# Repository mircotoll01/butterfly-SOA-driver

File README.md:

# Overview
This is an experimental slave module used to drive a optical devices with a butterfly package and integrated TEC. The driver can be operated from the header connector on the side.
The board was initially thought as a Laser Diode driver encased in butterfly packages, which usually integrate both the LD and a Peltier cell.
Since there is no standard pinouts in butterfly-type packages, this board routes all its power outputs and inputs to a row of headers, and all butterfly pins are routed to open headers as well, so that it is possible to route different parts of the board to different butterfly pins, whose position is numbered and indicated on silkscreen. 

# Pinout

|PIN|USAGE|INFO|
|-|-|-|
|1|3V3|Logic power supply, mandatory for the DAC that sets the optical device voltage|
|2|SCL|I2C clock pin for the DAC|
|3|SDA|I2C data pin for the DAC|
|4|$\overline{LDAC}$|Enable DAC register write mode|
|5|$RDY/\overline{BSY}$|This pin gives information on the DAC status|
|6|GND||
|7|TEC_EN|Enabling input for TEC|
|8|LD_MOD|LT3743's PWM input, when this signal is set to low all switching is disabled. Pull high if you don't plan to use it|
|9|CTRL_SEL|LT3743's switch for output voltage selection. The board has a double output capacitor topology that can be used to switch between two voltages. Useful if there is the need to keep an LD under the lasing threshold and periodically switch to a higher voltage.|
|10|ILD_MON|optical device current monitor|
|11|LD_EN|LT3743's enable pin|
|12|UNDRTMP_ALM|Sets if the temperature gets lower than a certain setpoint|
|13|OVRTMP_ALM|Sets if the temperature gets higher than a certain setpoint|
|14|ITEC_MON|TEC current monitor|

# Usage

The board was tested with a Basys3 as a master module and the firmware is available in this repository. If a basys3 is used to operate this driver connect its output pins in the following way (declared in the bays3's constraint file):

JA1     &rarr; OVRTMP_ALM  \
JA2     &rarr; UNDRTMP_ALM \
JA3     &rarr; LD_EN \
JA4     &rarr; CTRL_SEL \
JA5     &rarr; GND \
JA6     &rarr; 3V3 \
JA8     &rarr; TEC_EN \
JA9     &rarr; SDA \
JA10    &rarr; SCL \
JB1     &rarr; $\overline{LDAC}$  
\
To control the board with the Basys3 simply connect these pins and connect the board to the computer via USB. The given firmware will provide a rudimental serial interface that will control the state of the driver.
A simple python script can do the trick. the following one will work on linux:

```
import serial

ser = serial.Serial('/dev/ttyUSB1', baudrate=9600, bytesize=serial.EIGHTBITS, parity=serial.PARITY_NONE, stopbits=serial.STOPBITS_TWO,timeout=10)

while True:
    packet = bytearray(input("Waiting for a command: ").encode("ascii") + b'\n')

    ser.write(packet)

    for i in packet:
        print(ser.read())
    
```

#### Update
Now this repo provides a python script that gives a console to the user to send commands and see current parameters. The requirements for the python script are the following: 

- curses
- threading
- pyserial
- time
- re

### Command list

|COMMAND|INFO|
|-|-|
|OFF|Pulls LD_EN to low, disables all switching functions. Any other command will set LD_EN back to high|
|CCC|Activates the part of the circuit that supplies costant current to the optical component|
|TEC|Activates the Thermo-Electric Controller|
|PWM|Sets PWM mode with a certain duty cycle, set CTLL voltage first to operate the optical device in this mode|
|SET|Sets the selected register of the DAC to a set value|
|DBL|Sets double output voltage mode, the low and high thresholds have to be set first|

The SET command will accept the following attributes:

|ATTRIBUTE|INFO|
|-|-|
|CTLL| Modifies the lower voltage threshold CTRL_L. Note: this pin is internally clamped to 1.5V by the LT3743|
|CTLH| Modifies the higher voltage threshold CTRL_H. Note: this pin is internally clamped to 1.5V by the LT3743|
|TSET| Sets the voltage setpoint for the TEC's PID controller|
|MAXV| Sets the TEC's maximum operating voltage|

### Syntax
<table>
    <tr>
        <th>BASE COMMAND</th>
        <th>FIRST ATTRIBUTE</th>
        <th>SECOND ATTRIBUTE</th>
    </tr>
    <tr>
        <td>OFF</td>
        <td>None</td>
        <td>None</td>
    </tr>
    <tr>
        <td>CCC</td>
        <td>ON/OFF</td>
        <td>None</td>
    </tr>
    <tr>
        <td>TEC</td>
        <td>ON/OFF</td>
        <td>None</td>
    </tr>
    <tr>
        <td rowspan="4">SET</td>
        <td>CTLL</td>
        <td rowspan="2">Integer from 0 to 1500, which corresponds to a voltage output from the DAC that goes from 0 to 1.5V. This voltage sets the inductor current which charges its corresponding output capacitor.
        </td>
    </tr>
    <tr>
        <td>CTLH</td>
        <td></td>
    </tr>
    <tr>
        <td>TSET</td>
        <td>Integer from 0 to 1500, which corresponds to a voltage output from the DAC that goes from 0 to 1.5V.</td>
    </tr>
    <tr>
        <td>MAXV</td>
        <td>Integer from 0 to 5000. The program scales it down to reach a voltage output from the DAC that goes from 0 to 1.250V. 
        Since TEC voltage is set to 4*MAXV the range 0-5V range can be achieved.</td>
    </tr>
    <tr>
        <td>PWM</td>
        <td>Integer encoded in three ciphers from 000 to 100</td>
        <td>None</td>
    </tr>
    <tr>
        <td>DBL</td>
        <td>Integer encoded in three ciphers from 000 to 100</td>
        <td>None</td>
    </tr>
</table>

#### Update Note
The commands are not case sensitive anymore

### Examples

Turn on a SOA or an LD:

```
CCC ON
PWM 100
```

Enable PWM modulation

```
CCC ON
PWM XXX
```

Enable double threshold modulation

```
CCC ON
DBL XXX
```

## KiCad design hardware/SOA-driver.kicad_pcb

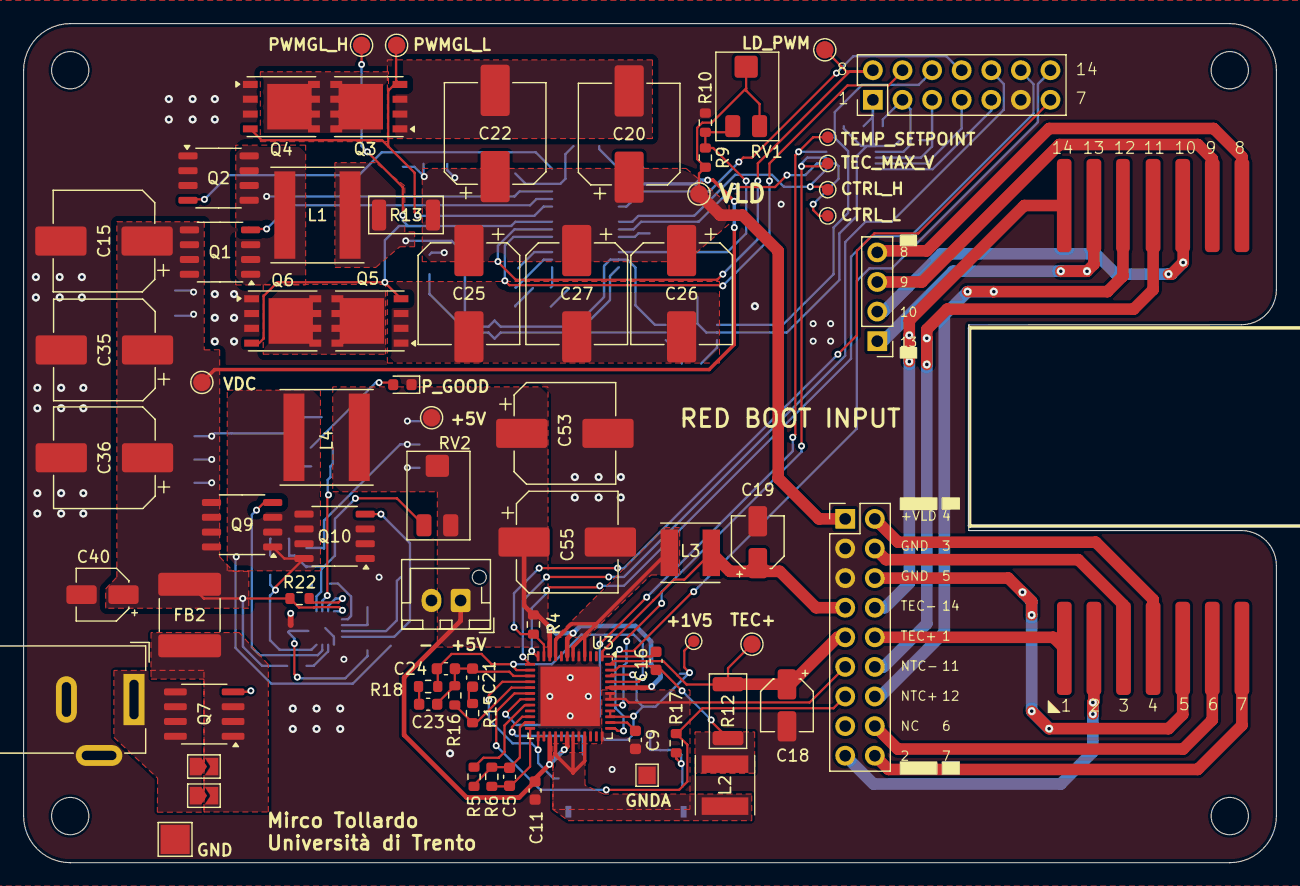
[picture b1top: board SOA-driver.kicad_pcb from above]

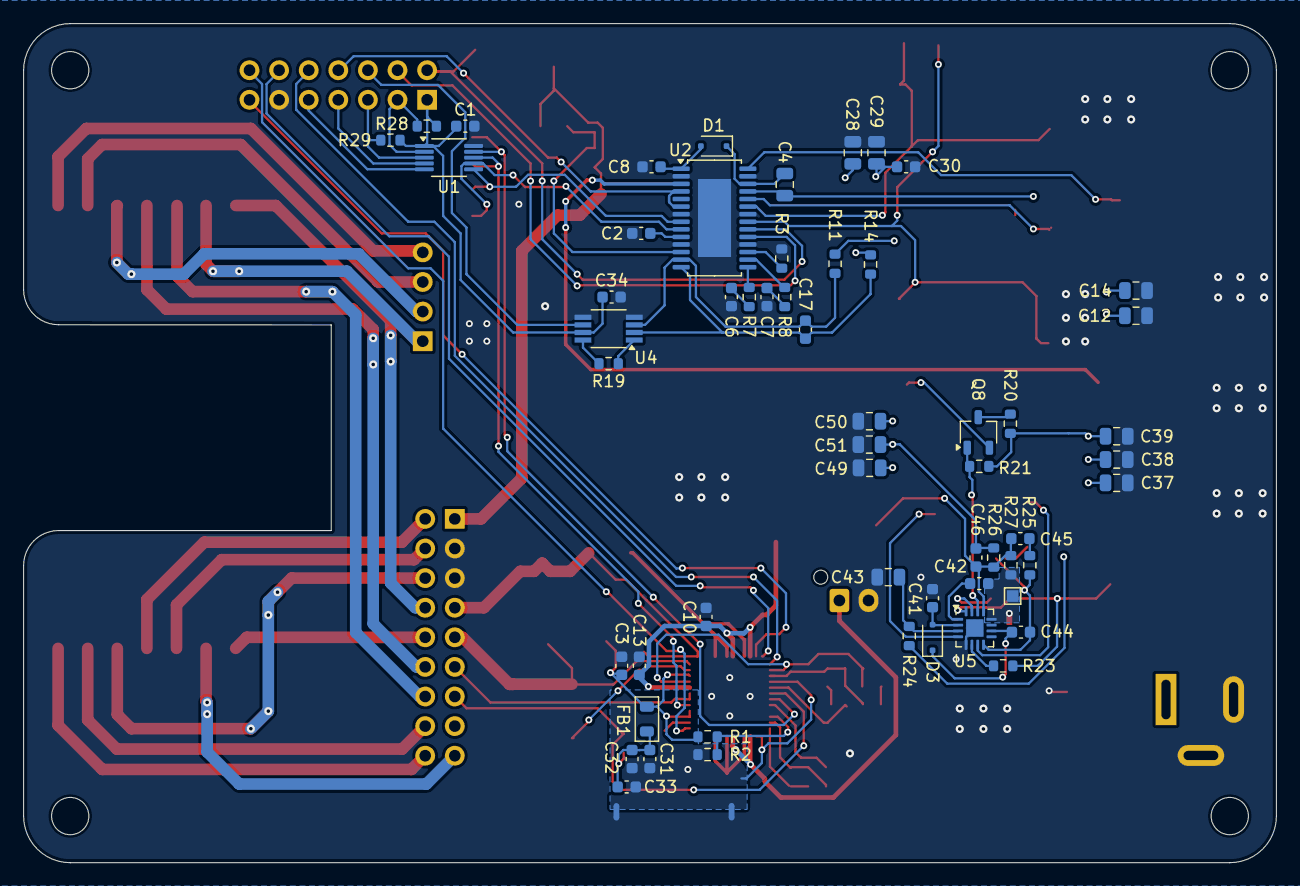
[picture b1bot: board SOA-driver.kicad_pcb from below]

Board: 2 copper layers, 107.5 x 72.0 mm, 136 parts (59 on the bottom side), 92 nets.

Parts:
C1, C3, C32, C34, C44, C45, C46: 100n; C_0603_1608Metric
C2, C9, C30, C33: 10n; C_0603_1608Metric
C4, C14, C29, C39, C43, C49: 100n; C_0805_2012Metric
C5, C31: 1u; C_0603_1608Metric
C6, C7: 2.2n; C_0603_1608Metric
C8, C10: 22u; C_0603_1608Metric
C11, C13, C23: 10u; C_0603_1608Metric
C12, C28, C38, C50: 1u; C_0805_2012Metric
C15, C20, C22, C25, C26, C27, C53, C55: 330u; CP_Elec_8x10.5
C16, C41, C42: 4u7; C_0603_1608Metric
C17: 33n; C_0603_1608Metric
C18, C19, C40: 1u; CP_Elec_4x5.4
C21, C24: 470n; C_0603_1608Metric
C35, C36: 220u; CP_Elec_8x10.5
C37, C51: 10u; C_0805_2012Metric
D1, D3: BAT54; D_SOD-323F
D2: LED; LED_0603_1608Metric
FB1: 110R; Ferrite_0805_2012Metric
FB2: 100; C_2220_5750Metric_Pad1.97x5.40mm_HandSolder
H1, H2, H3, H4: MountingHole; MountingHole_3.2mm_M3_ISO7380
J1: BASYS3; PinHeader_2x07_P2.54mm_Vertical
J2: BUTTERFLY; Butterfly_14pins_SMD
J3: Barrel_Jack_Switch; BarrelJack_Wuerth_6941xx301002
J4: SELECTOR; PinHeader_2x09_P2.54mm_Vertical
J5: SELECTOR_2; PinHeader_1x04_P2.54mm_Vertical
J6: 5V EXT; JST_XH_B2B-XH-AM_1x02_P2.50mm_Vertical
JP1, JP2: SolderJumper_2_Open; SolderJumper-2_P1.3mm_Open_TrianglePad1.0x1.5mm
L1, L4: 22u; L_Taiyo-Yuden_NR-80xx
L2, L3: 3u3; L_Taiyo-Yuden_NR-50xx
NT1, NT2, NT3: NetTie_2; NetTie-2_SMD_Pad0.5mm
Q1, Q2, Q9, Q10: RJK0355DSP; SOP-8_3.9x4.9mm_P1.27mm
Q3, Q4, Q5, Q6: SiRC18DP; PowerPAK_SO-8_Single
Q7: DMP3037LSS-13; SOIC-8_3.9x4.9mm_P1.27mm
Q8: 2N7002; TSOT-23
R1: 69.8k; R_0603_1608Metric
R2, R5: 20k; R_0603_1608Metric
R3: 40.2k; R_0603_1608Metric
R4, R10, R27, R29: 1k; R_0603_1608Metric
R6: 80.6k; R_0603_1608Metric
R7, R8: 806k; R_0603_1608Metric
R9, R20: 2k2; R_0603_1608Metric
R11, R14, R28: 10; R_0603_1608Metric
R12: 200m; R_2010_5025Metric
R13: 50m; R_2010_5025Metric
R15: 22k; R_0603_1608Metric
R16: 1M; R_0603_1608Metric
R17, R21, R22: 10k; R_0603_1608Metric
R18: 100k; R_0603_1608Metric
R19: 11K 0.1%; R_0603_1608Metric
R23: 100k 1%; R_0603_1608Metric
R24, R25: R_Small; R_0603_1608Metric
R26: 5k6; R_0603_1608Metric
RV1: 1k; Potentiometer_Bourns_3224X_Vertical
RV2: 10k; Potentiometer_Bourns_3224X_Vertical
TP1, TP8, TP9, TP10, TP11: TestPoint; TestPoint_Pad_D1.0mm
TP2: TestPoint; TestPoint_Pad_1.5x1.5mm
TP3, TP4, TP5, TP6, TP7, TP14, TP15: TestPoint; TestPoint_Pad_D1.5mm
TP12: TestPoint; TestPoint_Pad_2.5x2.5mm
TP13: TestPoint; TestPoint_Pad_1.0x1.0mm
U1: MCP4728; MSOP-10_3x3mm_P0.5mm
U2: LT3743; TSSOP-28-1EP_4.4x9.7mm_P0.65mm_EP2.85x6.7mm
U3: MAX1978; TQFN-48-1EP_7x7mm_P0.5mm_EP5.1x5.1mm
U4: INA333xxDGK; VSSOP-8_3.0x3.0mm_P0.65mm
U5: MIC2101; HVQFN-16-1EP_3x3mm_P0.5mm_EP1.5x1.5mm

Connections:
+1V5: C3.2, FB1.1, R1.1, TP1.1, U3.39 (MAXIP), U3.40 (MAXIN), U3.46 (REF)
+3V3: C1.1, C34.1, J1.1, R28.2, R29.2, U1.1 (VDD), U4.7 (V+)
+5V: C10.1, C11.1, C13.1, C46.2, C49.1, C50.1, C51.1, C53.1, C55.1, J6.1, L4.2, R4.1, R26.2, RV2.2, RV2.3, TP14.1, U3.7 (PVDD2), U3.10 (PVDD2), U3.27 (PVDD1), U3.30 (PVDD1), U3.44 (VDD)
/5V DCDC converter/DH: Q9.4 (G), U5.7 (DH)
/5V DCDC converter/DL: Q10.4 (G), U5.4 (DL)
/5V DCDC converter/FB: C45.1, C46.1, R26.1, R27.2, RV2.1, U5.13 (FB)
/SOA Driver/LD: C20.1, C22.1, C25.1, C26.1, C27.1, C28.1, C29.1, C30.1, J4.1, R9.2, R13.2, R14.2, RV1.2, RV1.3, TP4.1
/SOA Driver/NTC+: J4.13, R17.2, U3.18 (FB-)
/SOA Driver/PWMGH: Q5.4 (G), Q6.4 (G), TP5.1, U2.21 (PWMGH)
/SOA Driver/PWMGL: Q3.4 (G), Q4.4 (G), TP6.1, U2.23 (PWMGL)
/SOA Driver/Pin_1: J2.1, J4.10
/SOA Driver/Pin_2: J2.2, J4.17
/SOA Driver/Pin_3: J2.3, J4.4
/SOA Driver/Pin_4: J2.4, J4.2
/SOA Driver/Pin_5: J2.5, J4.6
/SOA Driver/Pin_6: J2.6, J4.16
/SOA Driver/Pin_7: J2.7, J4.18
/SOA Driver/Pin_8: J2.8, J5.4
/SOA Driver/Pin_9: J2.9, J5.3
/SOA Driver/Pin_10: J2.10, J5.2
/SOA Driver/Pin_11: J2.11, J4.12
/SOA Driver/Pin_12: J2.12, J4.14
/SOA Driver/Pin_13: J2.13, J5.1
/SOA Driver/Pin_14: J2.14, J4.8
/SOA Driver/SENSE+: C17.2, R11.1, U2.13 (SENSE+), U4.3 (+)
/SOA Driver/SENSE-: C17.1, R14.1, U2.14 (SENSE-), U4.2 (-)
/SOA Driver/SW: C4.2, L1.1, Q1.1 (S), Q1.2 (S), Q1.3 (S), Q2.5 (D), Q2.6 (D), Q2.7 (D), Q2.8 (D), U2.25 (SW)
/SOA Driver/TEC+: C18.1, J4.9, R12.2, TP3.1, U3.48 (OS1)
/SOA Driver/TEC-: C16.2, C19.1, J4.7, L3.2, U3.1 (OS2)
/TEC controller/1V5ADC: C31.1, C32.1, C33.1, FB1.2, R17.1
/TEC controller/BFB-: R5.2, U3.20 (BFB-)
/TEC controller/INT-: C21.1, C23.2, C24.1, R16.2, U3.15 (INT-)
/TEC controller/INTOUT: C24.2, R18.1, U3.14 (INTOUT), U3.45 (CTLI)
/TEC controller/MAXV_DAC: TP10.1, U1.8 (VOUTC), U3.41 (MAXV)
/TEC controller/TTEC_SETPOINT_DAC: TP11.1, U1.9 (VOUTD), U3.19 (FB+)
CTRL_H_DAC: TP8.1, U1.6 (VOUTA), U2.8 (CTRL_H)
CTRL_L_DAC: TP9.1, U1.7 (VOUTB), U2.9 (CTRL_L)
GND: C1.2, C2.1, C3.1, C6.2, C7.1, C8.1, C10.2, C11.2, C12.2, C13.2, C14.2, C15.2, C18.2, C19.2, C28.2, C29.2, C30.2, C34.2, C35.2, C36.2, C37.2, C38.2, C39.2, C40.2, C41.2, C43.1, C49.2, C50.2, C51.2, C53.2, C55.2, D2.1 (K), J1.11, J3.2, J3.3, J4.3, J4.5, J6.2, NT1.1, NT2.1, NT3.1, Q2.1 (S), Q2.2 (S), Q2.3 (S), Q4.1 (S), Q4.2 (S), Q4.3 (S), Q6.1 (S), Q6.2 (S), Q6.3 (S), Q7.4 (G), Q10.1 (S), Q10.2 (S), Q10.3 (S), R3.1, R10.1, TP12.1, U1.10 (VSS), U2.2 (GND), U2.7 (GND), U2.11 (GND), U2.18 (SYNC), U2.22 (GND), U2.27 (GND), U2.29 (GND), U3.3 (PGND2), U3.5 (PGND2), U3.32 (PGND1), U3.34 (PGND1), U3.49 (EP), U4.4 (V-), U4.5 (Ref), U5.5 (PGND), U5.17 (EP)
GND1: C42.2, NT2.2, R27.1, TP13.1, U5.12 (AGND)
GNDA: C9.2, C31.2, C32.2, C33.2, NT1.2, NT3.2, R2.2, TP2.1, U3.16 (AGND), U3.25 (AGND), U3.26 (AGND), U3.36 (FREQ), U3.42 (AGND), U3.43 (AGND)
ILD_MON: J1.6, U4.6
ITEC_MON: J1.14, U3.37 (ITEC)
LD_EN: J1.8, U2.4 (EN/UVLO), U2.6 (CTRL_T)
LD_MODULATION: TP7.1, U2.20 (PWM)
unnamed: C6.1, R7.2
unnamed: C7.2, R8.2
unnamed: C20.2, C22.2, Q3.1 (S), Q3.2 (S), Q3.3 (S)
unnamed: C21.2, R15.2
unnamed: C23.1, R18.2
unnamed: C25.2, C26.2, C27.2, Q5.1 (S), Q5.2 (S), Q5.3 (S)
unnamed: C45.2, R25.1
unnamed: C8.2, D1.2 (A), U2.1 (VCC_INT)
unnamed: C4.1, D1.1 (K), U2.26 (CBOOT)
unnamed: D2.2 (A), Q8.2 (S)
unnamed: C41.1, C42.1, D3.2 (A), U5.1 (VDD), U5.2 (PVDD)
unnamed: C44.2, D3.1 (K), U5.10 (BST)
unnamed: J3.1, JP1.1 (A), JP2.1 (A), Q7.5 (D), Q7.6 (D), Q7.7 (D), Q7.8 (D)
unnamed: FB2.1, JP1.2 (B), JP2.2 (B), Q7.1 (S), Q7.2 (S), Q7.3 (S)
unnamed: L1.2, R11.2, R13.1
unnamed: L2.1, U3.28 (LX1), U3.31 (LX1), U3.33 (LX1)
unnamed: L3.1, U3.4 (LX2), U3.6 (LX2), U3.9 (LX2)
unnamed: Q1.4 (G), U2.24 (HG)
unnamed: Q2.4 (G), U2.28 (LG)
unnamed: Q3.5 (D), Q4.5 (D)
unnamed: Q5.5 (D), Q6.5 (D)
unnamed: Q8.3 (D), R20.1
unnamed: Q8.1 (G), R21.1, U5.14 (PG)
unnamed: R19.1, U4.8 (Rg)
unnamed: R19.2, U4.1 (Rg)
unnamed: R9.1, R10.2, RV1.1, U2.12 (FB)
unnamed: R3.2, U2.17 (RT)
unnamed: C2.2, U2.10 (SS)
unnamed: R8.1, U2.16 (VCH)
unnamed: R7.1, U2.15 (VCL)
unnamed: R1.2, R2.1, U3.22 (AIN+)
unnamed: C5.1, R5.1, R6.1, U3.23 (AIN-)
unnamed: C5.2, R6.2, U3.24 (AOUT)
unnamed: C9.1, U3.38 (COMP)
unnamed: C16.1, L2.2, R12.1, U3.47 (CS)
unnamed: R15.1, R16.1, U3.17 (DIFOUT)
unnamed: R22.1, U5.15 (EN)
unnamed: R23.1, U5.6 (FREQ)
unnamed: C43.2, R24.1, U5.3 (ILIM)
unnamed: C44.1, L4.1, Q9.1 (S), Q9.2 (S), Q9.3 (S), Q10.5 (D), Q10.6 (D), Q10.7 (D), Q10.8 (D), R24.2, R25.2, U5.8 (SW)
OVERTMP_ALM: J1.12, U3.12 (~OT)
RDY/~BSY: J1.9, U1.5 (RDY/~BSY)
SCL: J1.3, R28.1, U1.2 (SCL)
SDA: J1.5, R29.1, U1.3 (SDA)
TEC_~SHD: R4.2, U3.11 (~SHD)
UNDERTMP_ALM: J1.10, U3.13 (~UT)
VDC: C12.1, C14.1, C15.1, C35.1, C36.1, C37.1, C38.1, C39.1, C40.1, FB2.2, Q1.5 (D), Q1.6 (D), Q1.7 (D), Q1.8 (D), Q9.5 (D), Q9.6 (D), Q9.7 (D), Q9.8 (D), R20.2, R21.2, R22.2, R23.2, TP15.1, U2.3 (VIN), U5.16 (VIN)
~LDAC: J1.7, U1.4 (~LDAC)

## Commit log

2024-04-15 Uploaded a slave module to drive a generic LD
2024-04-15 add README and gitignore
2024-04-17 small schematic correction, structural changes to the 5V buck on the pcb
2024-04-30 update PCB: fixed buck layout, concept layout for LD driver with LT3743
2024-05-08 Changed overall subsystem positions, TEC controller implemented, LD controller IC position to be reconsidered in order to have enough clearance after header connector is fully routed
2024-05-16 PCB routing completed, started uniforming components for smaller BOM
2024-05-16 small corrections to PCB, fixed some capacitors' voltage ratings and footprints to make BOM more uniform
2024-05-16 small fixes to PCB and silkscreen
2024-05-28 feat: made possible to swap butterfly pins for compatibility
2024-05-31 feat: added method to swap butterfly socket pins to adapt to multiple SOA SNs. Fixed routing imperfections and addes informative silkscreen
2024-06-24 fix: small corrections to the pcb, added PNs and store link to mouser for each component
2024-12-04 fix: shorted PVDD and VDD on MIC
2024-12-04 feat: added firmware and better dir management, updates gitignore for vivado files
2024-12-04 better structure for VHDL code
2024-12-04 MIT license
2024-12-10 feat: payload generation for I2C master
2024-12-10 fix: tidier schematic
2024-12-10 feat: added payload generation and management for MCP4728 and modulator to Control Unit
2024-12-12 feat: added UART communication block to set SOA driving parameters
2024-12-14 feat: dedicated UART parser, receiver now uses structural code. Control Unit now synthetizable
2024-12-18 fix: code synthetizable, partially fixed structure not synthetizing correctly
2025-02-26 feat: UART communication working, now with transmitter to verify that the sent packet is correct
2025-03-04 fix: timing fixed by lowering system clock to 10MHz, minor fixes to code
2025-03-15 fix: PWM mode now accepting values from 000 to 100
2025-03-15 feat: decent readme as user manual
2025-03-15 fix: errors and missing info on README
2025-03-15 fix: fix the damn markdown visualization on the damn README
2025-03-17 feat: added limitations in input integers in parser, minor fixes to readme
2025-05-19 feat: SPI monitor in python, UART transmission for ADC reading (untested)
2025-06-04 feat: new graphic interface to see currently stored values in driver's register, full bidirectional UART communication
2025-06-04 fix: minor fixes to modulator
2025-06-05 feat: parser with cleaner code and case insensitive, minor fixes to code
2025-06-06 fix: maajor fixes to code, partial simulation of control unit to check if modulation is working correctly
2025-06-06 fix: parser properly tested, partially clock sensitive to avoid wrong synthesis, modulator set to lower switching frequencies
2025-07-24 fix: I2C fixed and tested, modulation working with double threshold. feat: TEC and SOA can be enabled separately
2025-07-25 fix: ADC fully tested
2025-08-11 feat: syntethizing parser with output registers instead on using external reg, minor fixes to schematic and PCB
2025-08-12 feat: add coefficient calculations for tested QSOA-1550, minor fix to parser register
